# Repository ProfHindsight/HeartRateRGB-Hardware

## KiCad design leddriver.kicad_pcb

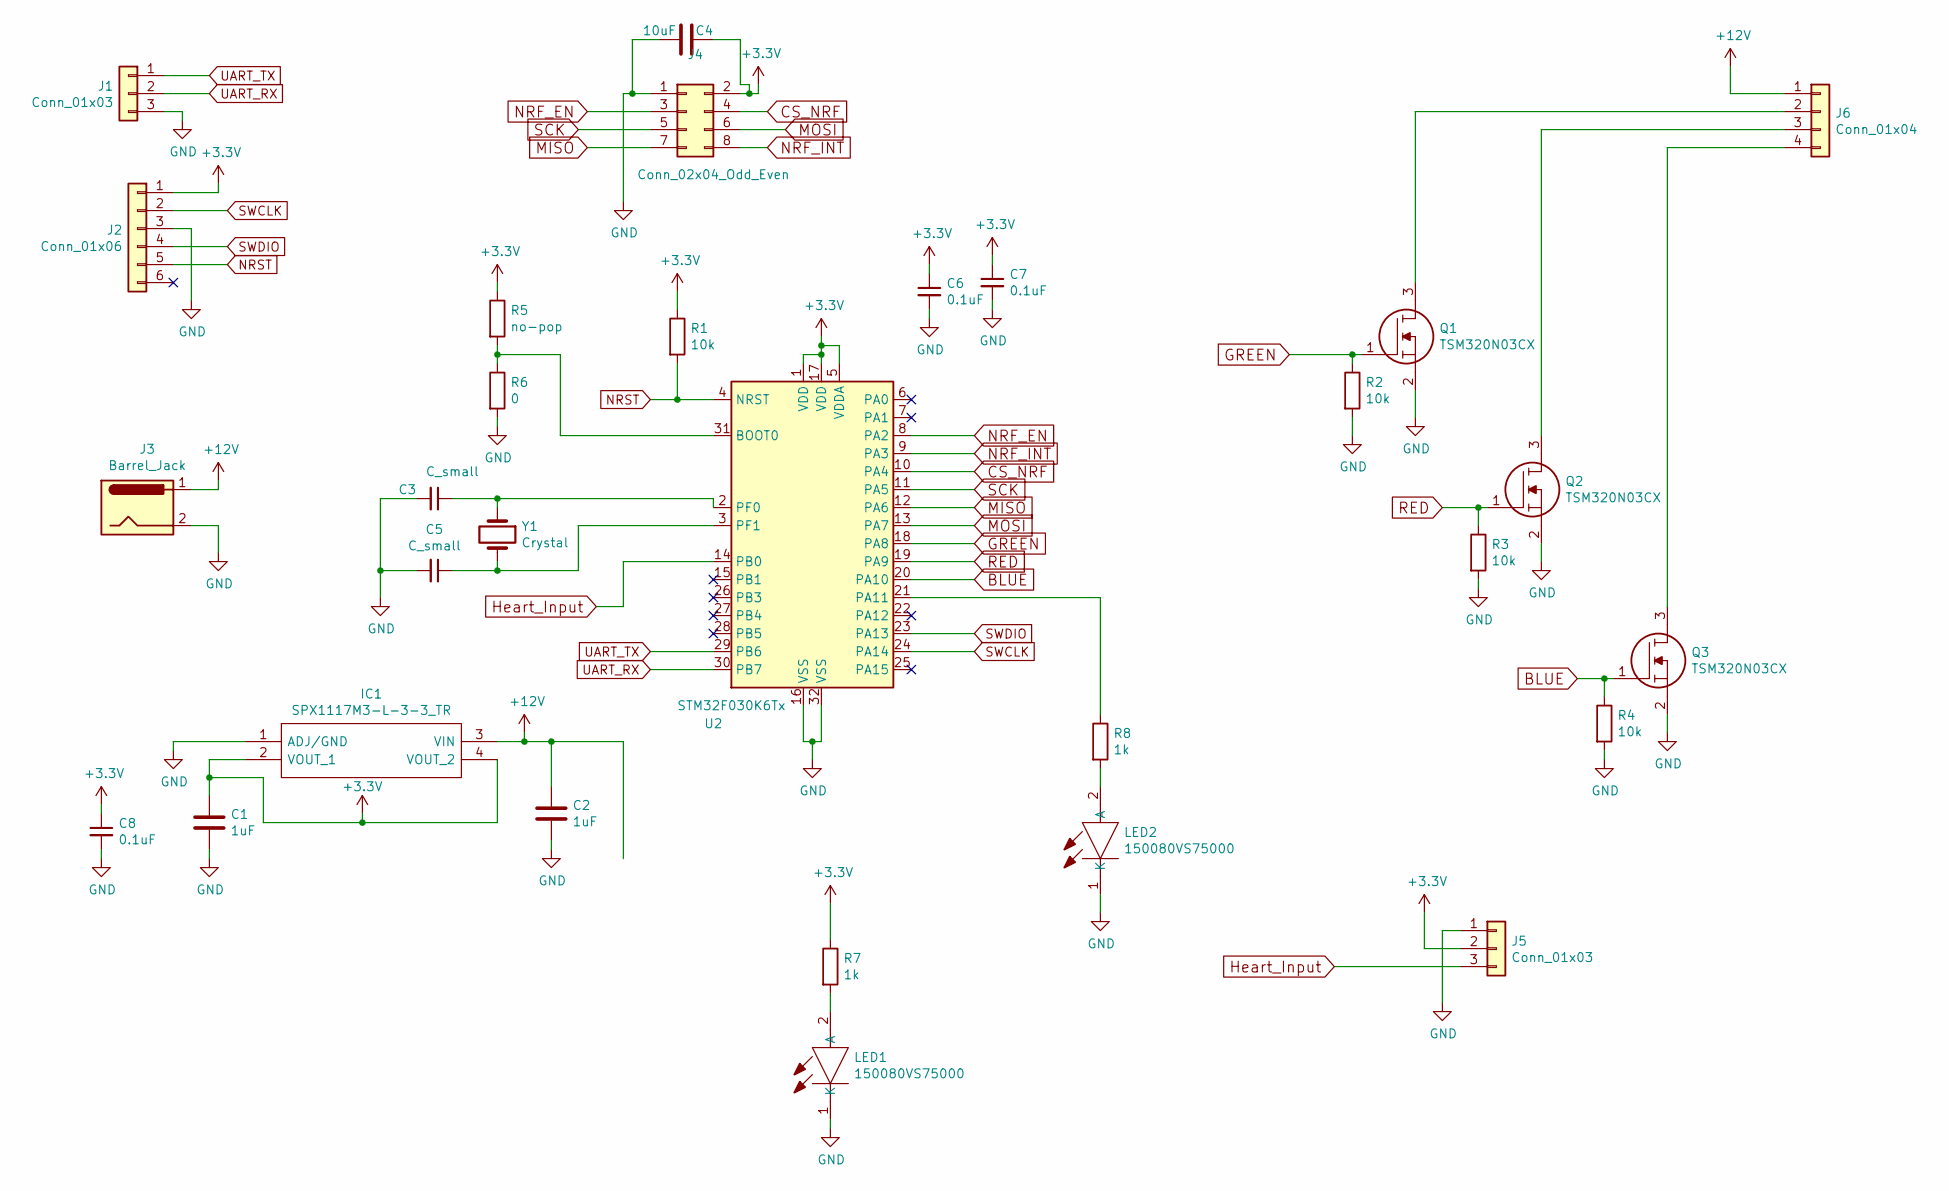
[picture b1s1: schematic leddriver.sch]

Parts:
C1, C2: 1uF; C_0805
C3, C5: C_small; C_0805
C4: 10uF; C_0805
C6, C7, C8: 0.1uF; C_0805
IC1: SPX1117M3-L-3-3_TR; SOT230P700X180-4N; Manufacturer_Part_Number SPX1117M3-L-3-3/TR
J1, J5: Conn_01x03; Pin_Header_Straight_1x03_Pitch2.54mm
J2: Conn_01x06; Pin_Header_Straight_1x06_Pitch2.54mm
J3: Barrel_Jack; 2_pin_barrel_jack
J4: Conn_02x04_Odd_Even; Pin_Header_Straight_2x04_Pitch2.54mm
J6: Conn_01x04; Pin_Header_Straight_1x04_Pitch2.54mm
LED1, LED2: 150080VS75000; LED_0805; Manufacturer_Part_Number 150080VS75000; Mouser Part Number 710-150080VS75000
Q1, Q2, Q3: TSM320N03CX; SOT95P280X130-3N; Manufacturer_Part_Number TSM320N03CX
R1, R2, R3, R4: 10k; R_0805
R5: no-pop; R_0402
R6: 0; R_0402
R7, R8: 1k; R_0805
U2: STM32F030K6Tx; QFP80P900X900X160-32N
Y1: Crystal; csm-7x

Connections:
+3V3: C1.2, C4.1, C6.1, C7.1, C8.1, IC1.2 (VOUT_1), IC1.4 (VOUT_2), J2.1, J4.2, J5.2, R1.1, R5.1, R7.1, U2.1 (VDD), U2.5 (VDDA), U2.17 (VDD)
+12V: C2.2, IC1.3 (VIN), J3.1, J6.1
BLUE: Q3.1, R4.1, U2.20 (PA10)
CS_NRF: J4.4, U2.10 (PA4)
GND: C1.1, C2.1, C3.2, C4.2, C5.2, C6.2, C7.2, C8.2, IC1.1 (ADJ/GND), J1.3, J2.3, J3.2, J4.1, J5.1, LED1.1 (K), LED2.1 (K), Q1.2, Q2.2, Q3.2, R2.2, R3.2, R4.2, R6.2, U2.16 (VSS), U2.32 (VSS)
GREEN: Q1.1, R2.1, U2.18 (PA8)
Heart_Input: J5.3, U2.14 (PB0)
MISO: J4.7, U2.12 (PA6)
MOSI: J4.6, U2.13 (PA7)
NRF_EN: J4.3, U2.8 (PA2)
NRF_INT: J4.8, U2.9 (PA3)
NRST: J2.5, R1.2, U2.4 (NRST)
unnamed: C3.1, U2.2 (PF0), Y1.1
unnamed: C5.1, U2.3 (PF1), Y1.2
unnamed: J6.2, Q1.3
unnamed: J6.3, Q2.3
unnamed: J6.4, Q3.3
unnamed: LED1.2 (A), R7.2
unnamed: LED2.2 (A), R8.2
unnamed: R5.2, R6.1, U2.31 (BOOT0)
unnamed: R8.1, U2.21 (PA11)
RED: Q2.1, R3.1, U2.19 (PA9)
SCK: J4.5, U2.11 (PA5)
SWCLK: J2.2, U2.24 (PA14)
SWDIO: J2.4, U2.23 (PA13)
UART_RX: J1.2, U2.30 (PB7)
UART_TX: J1.1, U2.29 (PB6)

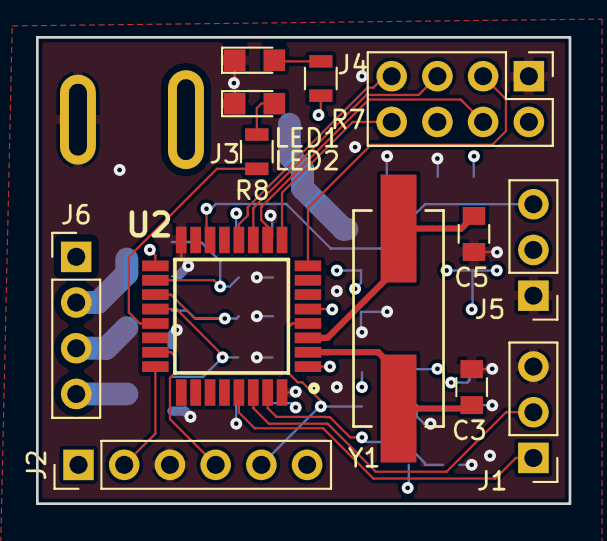
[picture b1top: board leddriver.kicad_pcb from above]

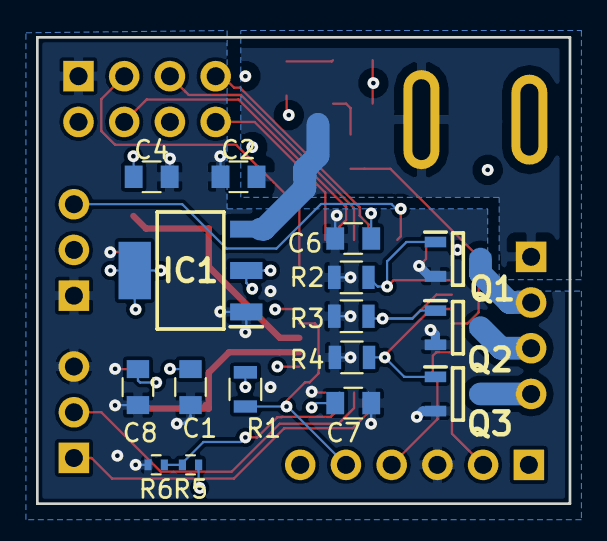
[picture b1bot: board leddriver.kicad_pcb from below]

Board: 4 copper layers, 29.6 x 25.9 mm, 30 parts (16 on the bottom side), 27 nets.
